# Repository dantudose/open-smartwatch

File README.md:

# Open-Smartwatch
An open hardware and software smartwatch.

## Main Hardware Diagram

This is a open-hardware wearable based on the ESP32 microcontroller. It is fully Arduino-compatible and it comes with the following features:
* ESP32-S3 Mini module (240MHz, WiFI, BLE, 512kB SRAM and 4MB Flash)
* GC9A01 1.28 inch color LCD, 240 x 240 pixels
* BMI085 6-axis inertial sensor (accelerometer and gyroscope)
* W25Q256JVEIQ 32MB external SPI Flash
* DRV2605 haptic driver
* SPI card reader
* 200mAh LiPo battery
* USB-C connector

## Repository Contents

* **/Hardware** - Eagle design files (.brd, .sch)
* **/Images** - Board images
* **/Mechanical** - Mechanical files for the case (.stl)
  
### Button Layout

 <div style='float:left'>
<table>
<thead>
  <tr>
    <th>Button</th>
    <th>ESP32 Pin</th>
  </tr></thead>
  <tbody>
  <tr>
    <td>UP</td>
    <td>IO11</td>
  </tr>
  <tr>
    <td>DOWN</td>
    <td>IO26</td>
  </tr>
  <tr>
    <td>BOOT</td>
    <td>IO0</td>
  </tr>
  <tr>
    <td>RESET</td>
    <td>EN</td>
  </tr>
  </tbody>
</table>
 </div>
<div style='float:right'>
   
  </div>

## Mechanical Dimensions

The watch has the overall dimensions of 43.5 x 48 x 18mm and supports standard 20mm straps.

## PCB Design

Two-layer PCB design.

## License Information

This product is _**open source**_! 

Please review the LICENSE file for license information.

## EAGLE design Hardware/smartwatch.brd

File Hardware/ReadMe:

Eagle CAD files for the schematic and board.

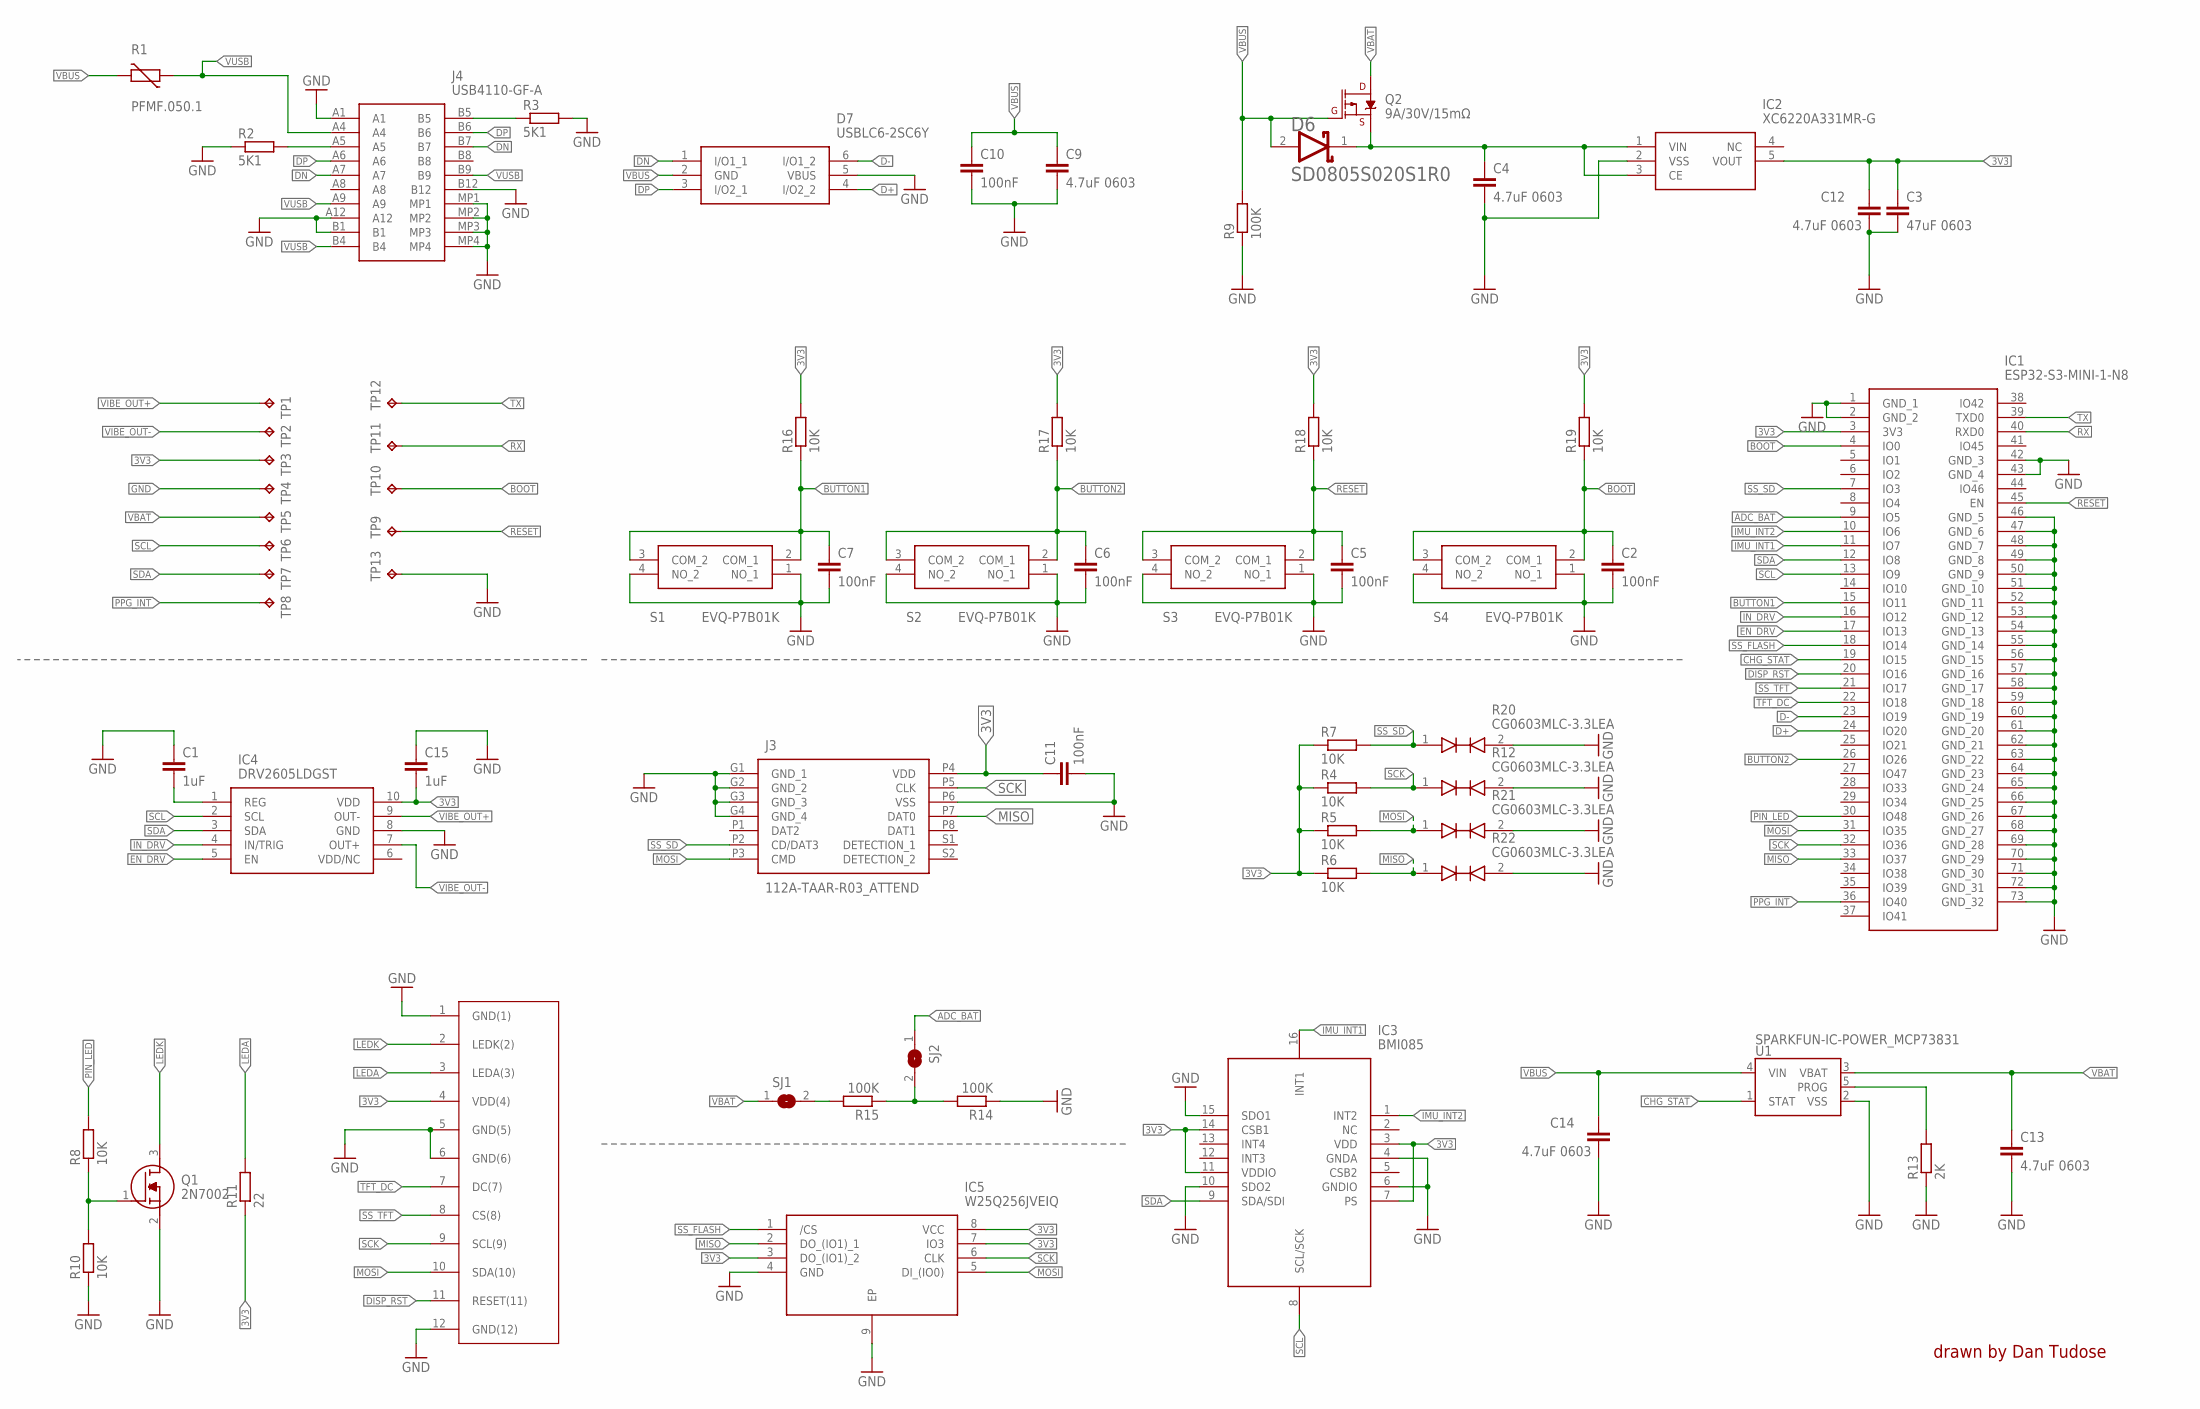
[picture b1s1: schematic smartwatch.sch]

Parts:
C1, C15: 1uF; EAGLE-LTSPICE_C0402
C2, C5, C6, C7, C10, C11: 100nF; EAGLE-LTSPICE_C0402
C3: 47uF 0603; RCL_C0603
C4, C9, C12, C13, C14: 4.7uF 0603; RCL_C0603
CON1: LCD_FPC
D6: AVX---SD0805S020S1R0_AVX_SD0805S020S1R0AVX_SD0805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; AVX---SD0805S020S1R0_AVX_SD0805S020S1R0_0
D7: USBLC6-2SC6Y; SOT95P280X145-6N
IC1: ESP32-S3-MINI-1-N8; ESP32S3MINI1N8
IC2: XC6220A331MR-G; SOT95P280X120-5N
IC3: BMI085
IC4: DRV2605LDGST; SOP50P490X110-10N
IC5: W25Q256JVEIQ; SON127P800X600X80-9N
J3: 112A-TAAR-R03_ATTEND; 112ATAARR03ATTEND
J4: USB4110-GF-A; USB4110GFA
Q1: 2N7002; SOT96P240X120-3N
Q2: 9A/30V/15mΩ; SPARKFUN-DISCRETESEMI_SOT23-3
R1: PFMF.050.1; VARISTOR_CT/CN1812
R2, R3: 5K1; EAGLE-LTSPICE_R0402
R4, R5, R6, R7, R8, R10, R16, R17, R18, R19: 10K; EAGLE-LTSPICE_R0402
R9, R14, R15: 100K; EAGLE-LTSPICE_R0402
R11: 22; EAGLE-LTSPICE_R0402
R12, R20, R21, R22: CG0603MLC-3.3LEA; DIONC1608X61N
R13: 2K; EAGLE-LTSPICE_R0402
S1, S2, S3, S4: EVQ-P7B01K; EVQP7B01K
SJ1, SJ2: SJ
TP1, TP2, TP3, TP4, TP5, TP6, TP7, TP8, TP9, TP10, TP11, TP12, TP13: TPTP20R; TP20R
U1: SPARKFUN-IC-POWER_MCP73831; SPARKFUN-IC-POWER_SOT23-5

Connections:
3V3: C3.1, C11.1, C12.1, C15.2, CON1.4 (VDD(4)), IC1.3 (3V3), IC2.5 (VOUT), IC3.3 (VDD), IC3.7 (PS), IC3.11 (VDDIO), IC3.14 (CSB1), IC4.10 (VDD), IC5.3 (DO_(IO1)_2), IC5.7 (IO3), IC5.8 (VCC), J3.P4 (VDD), R4.1, R5.1, R6.1, R7.1, R11.1, R16.2, R17.2, R18.2, R19.2, TP3.TP
ADC_BAT: IC1.9 (IO5), SJ2.1
BOOT: C2.1, IC1.4 (IO0), R19.1, S4.2 (COM_1), S4.3 (COM_2), TP10.TP
BUTTON1: C7.1, IC1.15 (IO11), R16.1, S1.2 (COM_1), S1.3 (COM_2)
BUTTON2: C6.1, IC1.26 (IO26), R17.1, S2.2 (COM_1), S2.3 (COM_2)
CHG_STAT: IC1.19 (IO15), U1.1 (STAT)
D+: D7.4 (I/O2_2), IC1.24 (IO20)
D-: D7.6 (I/O1_2), IC1.23 (IO19)
DISP_RST: CON1.11 (RESET(11)), IC1.20 (IO16)
DN: D7.1 (I/O1_1), J4.A7, J4.B7
DP: D7.3 (I/O2_1), J4.A6, J4.B6
EN_DRV: IC1.17 (IO13), IC4.5 (EN)
GND: C1.1, C2.2, C3.2, C4.2, C5.2, C6.2, C7.2, C9.2, C10.2, C11.2, C12.2, C13.2, C14.2, C15.1, CON1.1 (GND(1)), CON1.5 (GND(5)), CON1.6 (GND(6)), CON1.12 (GND(12)), D7.5 (VBUS), IC1.1 (GND_1), IC1.2 (GND_2), IC1.42 (GND_3), IC1.43 (GND_4), IC1.46 (GND_5), IC1.47 (GND_6), IC1.48 (GND_7), IC1.49 (GND_8), IC1.50 (GND_9), IC1.51 (GND_10), IC1.52 (GND_11), IC1.53 (GND_12), IC1.54 (GND_13), IC1.55 (GND_14), IC1.56 (GND_15), IC1.57 (GND_16), IC1.58 (GND_17), IC1.59 (GND_18), IC1.60 (GND_19), IC1.61 (GND_20), IC1.62 (GND_21), IC1.63 (GND_22), IC1.64 (GND_23), IC1.65 (GND_24), IC1.66 (GND_25), IC1.67 (GND_26), IC1.68 (GND_27), IC1.69 (GND_28), IC1.70 (GND_29), IC1.71 (GND_30), IC1.72 (GND_31), IC1.73 (GND_32), IC2.2 (VSS), IC3.4 (GNDA), IC3.6 (GNDIO), IC3.10 (SDO2), IC3.15 (SDO1), IC4.8 (GND), IC5.4 (GND), IC5.9 (EP), J3.G1 (GND_1), J3.G2 (GND_2), J3.G3 (GND_3), J3.G4 (GND_4), J3.P6 (VSS), J4.A1, J4.A12, J4.B1, J4.B12, J4.MP1, J4.MP2, J4.MP3, J4.MP4, Q1.2 (S), R2.1, R3.2, R9.1, R10.1, R12.2, R13.1, R14.1, R20.2, R21.2, R22.2, S1.1 (NO_1), S1.4 (NO_2), S2.1 (NO_1), S2.4 (NO_2), S3.1 (NO_1), S3.4 (NO_2), S4.1 (NO_1), S4.4 (NO_2), TP4.TP, TP13.TP, U1.2 (VSS)
IMU_INT1: IC1.11 (IO7), IC3.16 (INT1)
IMU_INT2: IC1.10 (IO6), IC3.1 (INT2)
IN_DRV: IC1.16 (IO12), IC4.4 (IN/TRIG)
LEDA: CON1.3 (LEDA(3)), R11.2
LEDK: CON1.2 (LEDK(2)), Q1.3 (D)
MISO: IC1.33 (IO37), IC5.2 (DO_(IO1)_1), J3.P7 (DAT0), R6.2, R22.1
MOSI: CON1.10 (SDA(10)), IC1.31 (IO35), IC5.5 (DI_(IO0)), J3.P3 (CMD), R5.2, R21.1
unnamed: C1.2, IC4.1 (REG)
unnamed: C4.1, D6.1 (CATHODE), IC2.1 (VIN), IC2.3 (CE), Q2.2 (S)
unnamed: J4.A5, R2.2
unnamed: R13.2, U1.5 (PROG)
unnamed: J4.B5, R3.1
unnamed: Q1.1 (G), R8.1, R10.2
unnamed: R14.2, R15.1, SJ2.2
unnamed: R15.2, SJ1.2
PIN_LED: IC1.30 (IO48), R8.2
PPG_INT: IC1.36 (IO40), TP8.TP
RESET: C5.1, IC1.45 (EN), R18.1, S3.2 (COM_1), S3.3 (COM_2), TP9.TP
RX: IC1.40 (RXD0), TP11.TP
SCK: CON1.9 (SCL(9)), IC1.32 (IO36), IC5.6 (CLK), J3.P5 (CLK), R4.2, R12.1
SCL: IC1.13 (IO9), IC3.8 (SCL/SCK), IC4.2 (SCL), TP6.TP
SDA: IC1.12 (IO8), IC3.9 (SDA/SDI), IC4.3 (SDA), TP7.TP
SS_FLASH: IC1.18 (IO14), IC5.1 (/CS)
SS_SD: IC1.7 (IO3), J3.P2 (CD/DAT3), R7.2, R20.1
SS_TFT: CON1.8 (CS(8)), IC1.21 (IO17)
TFT_DC: CON1.7 (DC(7)), IC1.22 (IO18)
TX: IC1.39 (TXD0), TP12.TP
VBAT: C13.1, Q2.3 (D), SJ1.1, TP5.TP, U1.3 (VBAT)
VBUS: C9.1, C10.1, C14.1, D6.2 (ANODE), D7.2 (GND), Q2.1 (G), R1.2, R9.2, U1.4 (VIN)
VIBE_OUT+: IC4.9 (OUT-), TP1.TP
VIBE_OUT-: IC4.7 (OUT+), TP2.TP
VUSB: J4.A4, J4.A9, J4.B4, J4.B9, R1.1

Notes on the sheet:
drawn by Dan Tudose

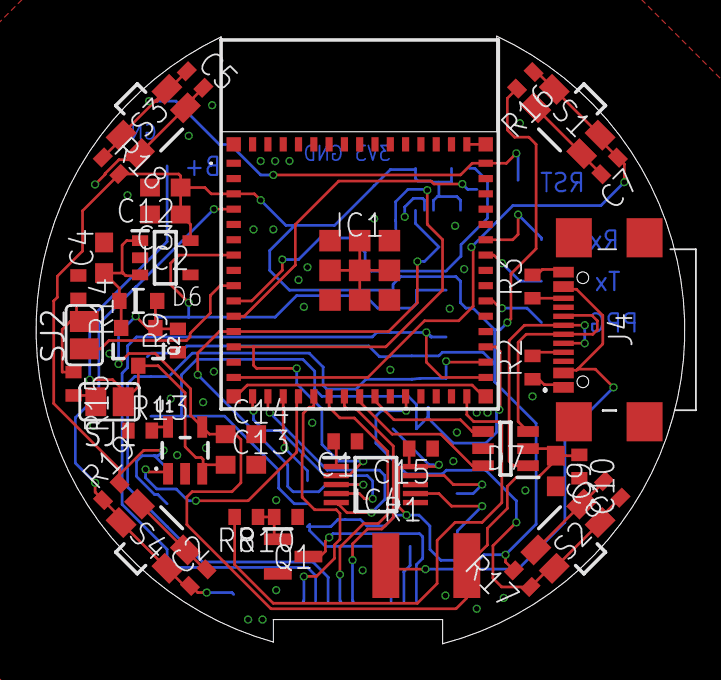
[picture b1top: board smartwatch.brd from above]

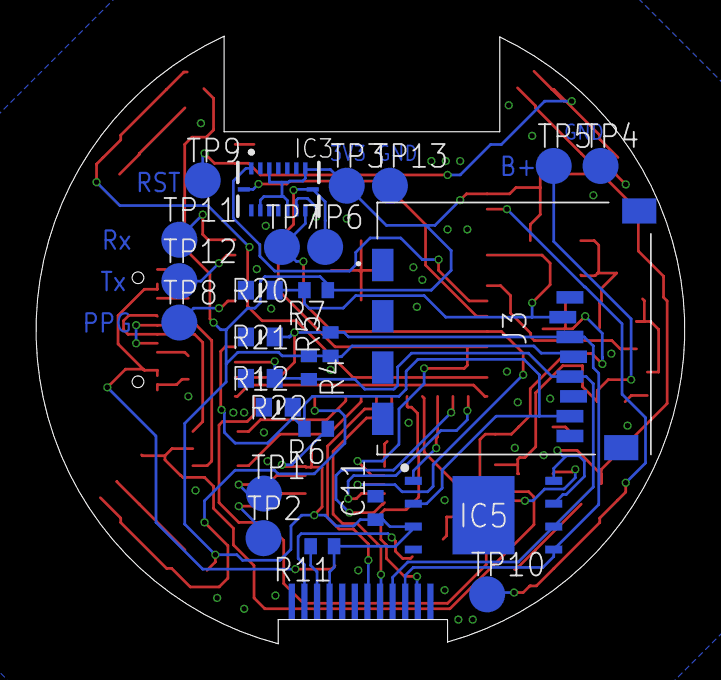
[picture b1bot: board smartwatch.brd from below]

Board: 2 copper layers, 36.0 x 33.8 mm, 68 parts (27 on the bottom side), 45 nets.
